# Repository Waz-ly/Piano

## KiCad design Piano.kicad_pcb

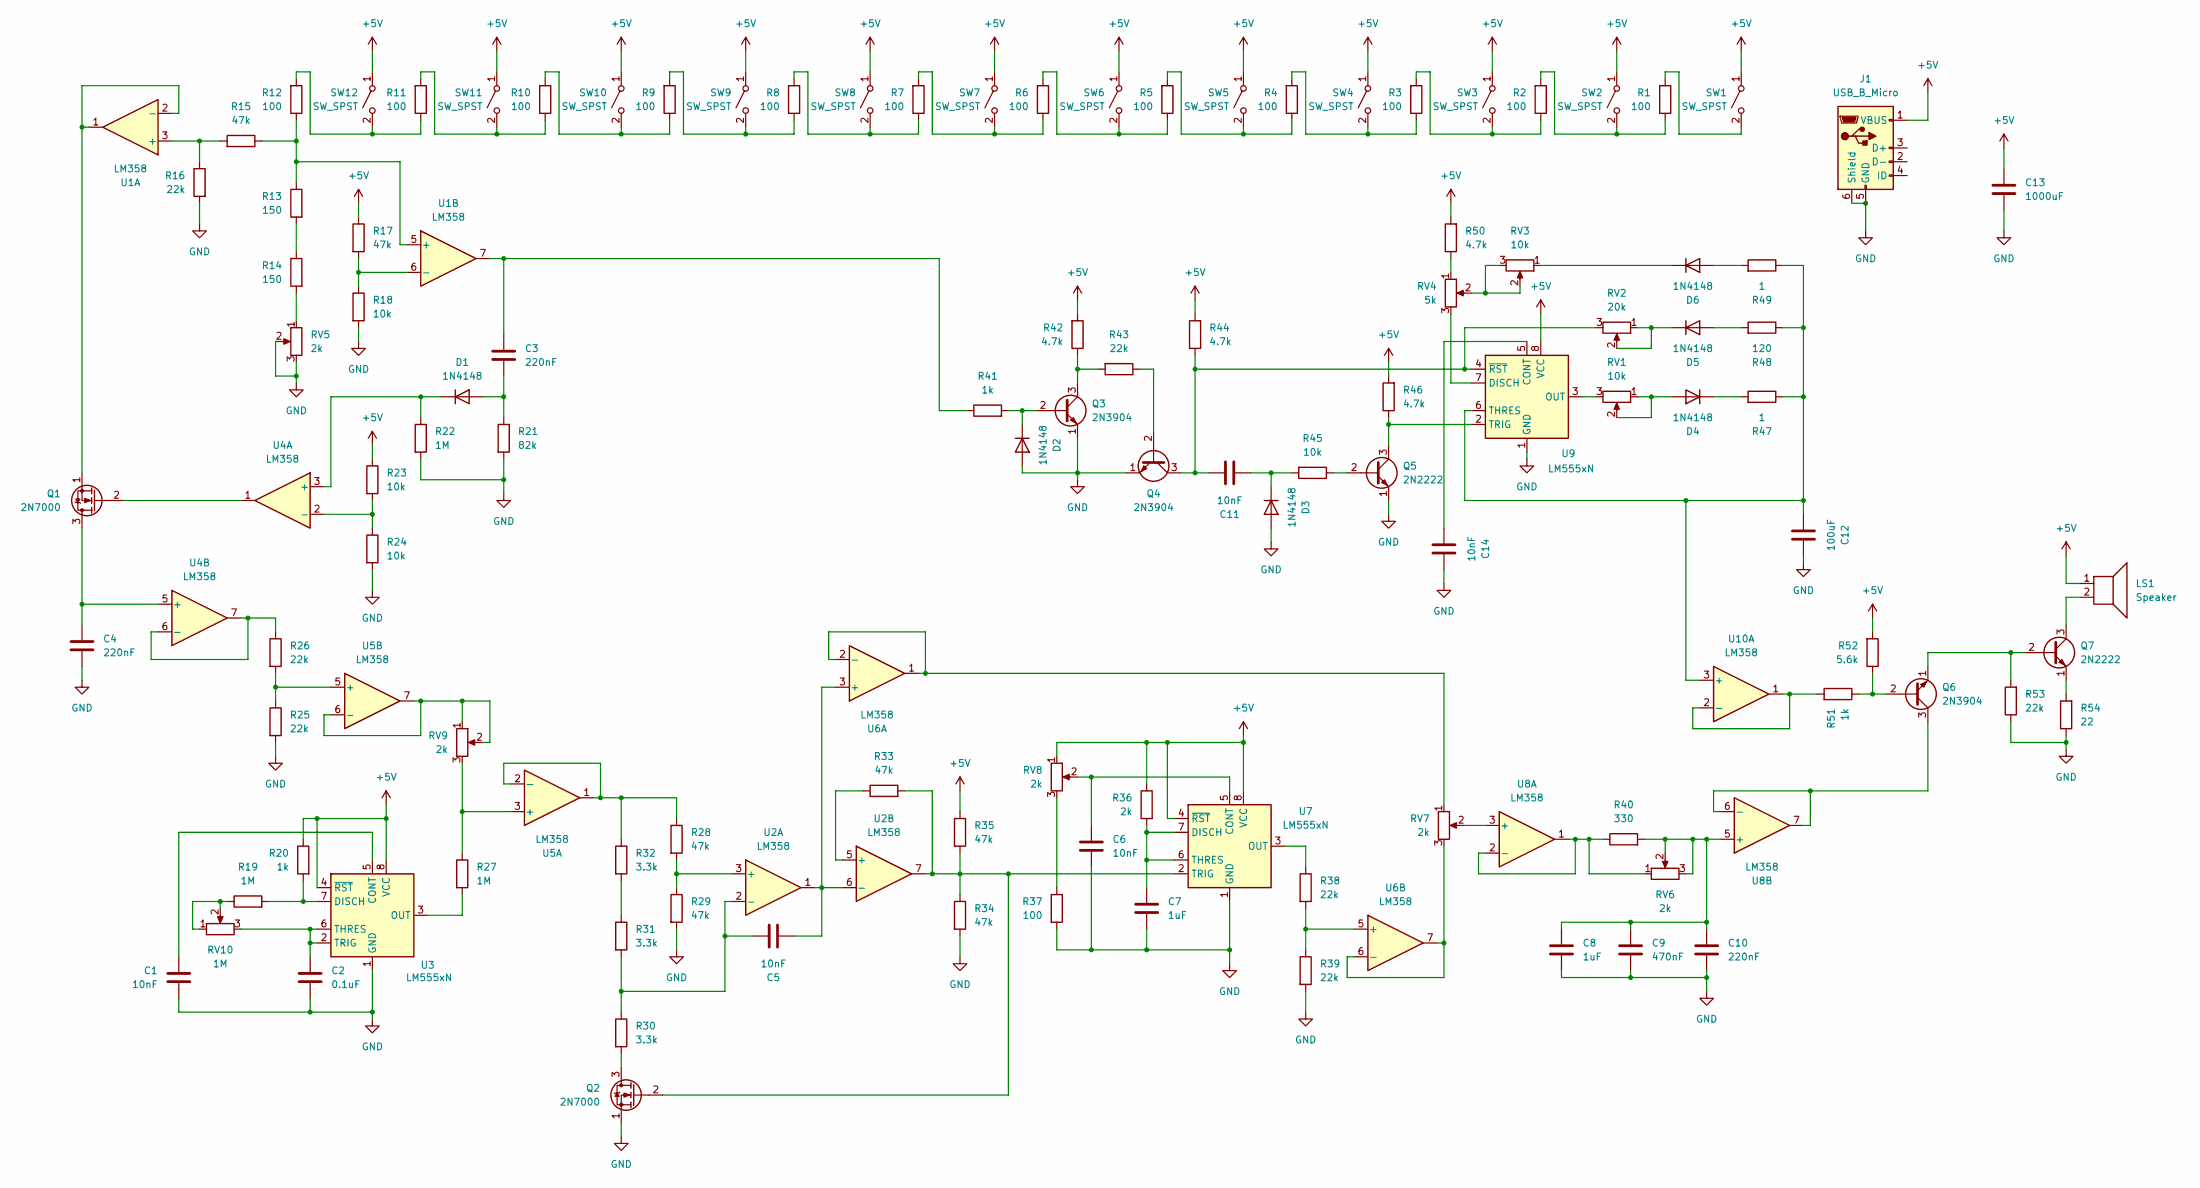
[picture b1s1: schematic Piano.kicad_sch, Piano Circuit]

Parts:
C1, C5, C6, C11, C14: 10nF; C_Rect_L7.2mm_W3.5mm_P5.00mm
C2: 0.1uF; C_Horizontal_D4.0mm_H7.0mm_P1.50mm
C3, C4, C10: 220nF; C_Rect_L7.2mm_W3.5mm_P5.00mm
C7, C8: 1uF; C_Axial_L5.1mm_D3.1mm_P10.00mm_Horizontal
C9: 470nF; C_Rect_L7.2mm_W3.5mm_P5.00mm
C12: 100uF; C_Horizontal_D5.0mm_H11.0mm_P2.00mm
C13: 1000uF; C_Horizontal_D10.0mm_H16.0mm_P5.00mm
D1, D2, D3, D4, D5, D6: 1N4148; D_DO-35_SOD27_P7.62mm_Horizontal
J1: USB_B_Micro; USB_Micro-B_XKB_U254-051T-4BH83-F1S
LS1: Speaker; PinHeader_1x02_P2.54mm_Vertical
Q1, Q2: 2N7000; TO-92_Inline
Q3, Q4, Q6: 2N3904; TO-92_Inline
Q5, Q7: 2N2222; TO-92_Inline
R1, R2, R3, R4, R5, R6, R7, R8, R9, R10, R11, R12, R37: 100; R_Axial_DIN0207_L6.3mm_D2.5mm_P10.16mm_Horizontal
R13, R14: 150; R_Axial_DIN0207_L6.3mm_D2.5mm_P10.16mm_Horizontal
R15, R17, R28, R29, R33, R34, R35: 47k; R_Axial_DIN0207_L6.3mm_D2.5mm_P10.16mm_Horizontal
R16, R25, R26, R38, R39, R43, R53: 22k; R_Axial_DIN0207_L6.3mm_D2.5mm_P10.16mm_Horizontal
R18, R23, R24, R45: 10k; R_Axial_DIN0207_L6.3mm_D2.5mm_P10.16mm_Horizontal
R19, R22, R27: 1M; R_Axial_DIN0207_L6.3mm_D2.5mm_P10.16mm_Horizontal
R20, R41, R51: 1k; R_Axial_DIN0207_L6.3mm_D2.5mm_P10.16mm_Horizontal
R21: 82k; R_Axial_DIN0207_L6.3mm_D2.5mm_P10.16mm_Horizontal
R30, R31, R32: 3.3k; R_Axial_DIN0207_L6.3mm_D2.5mm_P10.16mm_Horizontal
R36: 2k; R_Axial_DIN0207_L6.3mm_D2.5mm_P10.16mm_Horizontal
R40: 330; R_Axial_DIN0207_L6.3mm_D2.5mm_P10.16mm_Horizontal
R42, R44, R46, R50: 4.7k; R_Axial_DIN0207_L6.3mm_D2.5mm_P10.16mm_Horizontal
R47, R49: 1; R_Axial_DIN0207_L6.3mm_D2.5mm_P10.16mm_Horizontal
R48: 120; R_Axial_DIN0207_L6.3mm_D2.5mm_P10.16mm_Horizontal
R52: 5.6k; R_Axial_DIN0207_L6.3mm_D2.5mm_P10.16mm_Horizontal
R54: 22; R_Axial_DIN0207_L6.3mm_D2.5mm_P10.16mm_Horizontal
RV1, RV3: 10k; Inset_Potentiometer
RV2: 20k; Inset_Potentiometer
RV4: 5k; Inset_Potentiometer
RV5, RV6, RV7, RV8, RV9: 2k; Inset_Potentiometer
RV10: 1M; Inset_Potentiometer
SW1, SW2, SW3, SW4, SW5, SW6, SW7, SW8, SW9, SW10, SW11, SW12: SW_SPST; SW_Cherry_MX_Plate_1.00u
U1, U2, U4, U5, U6, U8, U10: LM358; DIP-8_W7.62mm
U3, U7, U9: LM555xN; DIP-8_W7.62mm

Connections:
+5V: C13.1, J1.1 (VBUS), LS1.1, R17.1, R20.1, R23.1, R35.1, R36.1, R42.2, R44.2, R46.2, R50.2, R52.2, RV8.1, SW1.1 (A), SW2.1 (A), SW3.1 (A), SW4.1 (A), SW5.1 (A), SW6.1 (A), SW7.1 (A), SW8.1 (A), SW9.1 (A), SW10.1 (A), SW11.1 (A), SW12.1 (A), U1.8 (V+), U2.8 (V+), U3.4 (~RST), U3.8 (VCC), U4.8 (V+), U5.8 (V+), U6.8 (V+), U7.4 (~RST), U7.8 (VCC), U8.8 (V+), U9.8 (VCC), U10.8 (V+)
GND: C1.2, C2.2, C4.2, C6.2, C7.2, C8.2, C9.2, C10.2, C12.1, C13.2, C14.1, D2.2 (A), D3.2 (A), J1.5 (GND), J1.6 (Shield), Q2.1 (S), Q3.1 (E), Q4.1 (E), Q5.1 (E), R16.2, R18.2, R21.2, R22.2, R24.2, R25.2, R29.2, R34.2, R37.2, R39.2, R53.1, R54.1, RV5.2, RV5.3, U1.4 (V-), U2.4 (V-), U3.1 (GND), U4.4 (V-), U5.4 (V-), U6.4 (V-), U7.1 (GND), U8.4 (V-), U9.1 (GND), U10.4 (V-)
unnamed: C3.1, R41.1, U1.7
unnamed: C3.2, D1.2 (A), R21.1
unnamed: D1.1 (K), R22.1, U4.3 (+)
unnamed: D2.1 (K), Q3.2 (B), R41.2
unnamed: C11.2, D3.1 (K), R45.2
unnamed: D4.2 (A), RV1.1, RV1.2
unnamed: D4.1 (K), R47.2
unnamed: D5.2 (A), R48.2
unnamed: D5.1 (K), RV2.1, RV2.2
unnamed: D6.2 (A), R49.2
unnamed: D6.1 (K), RV3.1
unnamed: C4.1, Q1.3 (D), U4.5 (+)
unnamed: Q1.2 (G), U4.1
unnamed: Q1.1 (S), U1.1, U1.2 (-)
unnamed: Q2.3 (D), R30.2
unnamed: Q2.2 (G), R33.2, R34.1, R35.2, U2.7, U7.2 (TRIG)
unnamed: Q3.3 (C), R42.1, R43.2
unnamed: Q4.2 (B), R43.1
unnamed: C11.1, Q4.3 (C), R44.1, RV2.3, U9.4 (~RST)
unnamed: Q5.2 (B), R45.1
unnamed: Q5.3 (C), R46.1, U9.2 (TRIG)
unnamed: Q6.2 (B), R51.1, R52.1
unnamed: Q6.3 (C), U8.6 (-), U8.7
unnamed: Q6.1 (E), Q7.2 (B), R53.2
unnamed: LS1.2, Q7.3 (C)
unnamed: Q7.1 (E), R54.2
unnamed: R13.2, R14.1
unnamed: R14.2, RV5.1
unnamed: R19.1, RV10.1, RV10.2
unnamed: R31.1, R32.2
unnamed: R37.1, RV8.3
unnamed: R50.1, RV4.1
unnamed: RV3.2, RV3.3, RV4.2
unnamed: R1.2, SW1.2 (B)
unnamed: R1.1, R2.2, SW2.2 (B)
unnamed: R2.1, R3.2, SW3.2 (B)
unnamed: R3.1, R4.2, SW4.2 (B)
unnamed: R4.1, R5.2, SW5.2 (B)
unnamed: R5.1, R6.2, SW6.2 (B)
unnamed: R6.1, R7.2, SW7.2 (B)
unnamed: R7.1, R8.2, SW8.2 (B)
unnamed: R8.1, R9.2, SW9.2 (B)
unnamed: R9.1, R10.2, SW10.2 (B)
unnamed: R10.1, R11.2, SW11.2 (B)
unnamed: R11.1, R12.2, SW12.2 (B)
unnamed: R15.2, R16.1, U1.3 (+)
unnamed: R12.1, R13.1, R15.1, U1.5 (+)
unnamed: R17.2, R18.1, U1.6 (-)
unnamed: R28.2, R29.1, U2.3 (+)
unnamed: C5.1, R30.1, R31.2, U2.2 (-)
unnamed: R33.1, U2.5 (+)
unnamed: C5.2, U2.1, U2.6 (-), U6.3 (+)
unnamed: C1.1, U3.5 (CONT)
unnamed: R19.2, R20.2, U3.7 (DISCH)
unnamed: R27.2, U3.3 (OUT)
unnamed: C2.1, RV10.3, U3.2 (TRIG), U3.6 (THRES)
unnamed: R23.2, R24.1, U4.2 (-)
unnamed: R26.1, U4.6 (-), U4.7
unnamed: R27.1, RV9.3, U5.3 (+)
unnamed: R28.1, R32.1, U5.1, U5.2 (-)
unnamed: R25.1, R26.2, U5.5 (+)
unnamed: RV9.1, RV9.2, U5.6 (-), U5.7
unnamed: RV7.1, U6.1, U6.2 (-)
unnamed: R38.2, R39.1, U6.5 (+)
unnamed: RV7.3, U6.6 (-), U6.7
unnamed: C6.1, RV8.2, U7.5 (CONT)
unnamed: C7.1, R36.2, U7.6 (THRES), U7.7 (DISCH)
unnamed: R38.1, U7.3 (OUT)
unnamed: RV7.2, U8.3 (+)
unnamed: R40.1, RV6.1, U8.1, U8.2 (-)
unnamed: C8.1, C9.1, C10.1, R40.2, RV6.2, RV6.3, U8.5 (+)
unnamed: C14.2, U9.5 (CONT)
unnamed: RV4.3, U9.7 (DISCH)
unnamed: RV1.3, U9.3 (OUT)
unnamed: C12.2, R47.1, R48.1, R49.1, U9.6 (THRES), U10.3 (+)
unnamed: R51.2, U10.1, U10.2 (-)

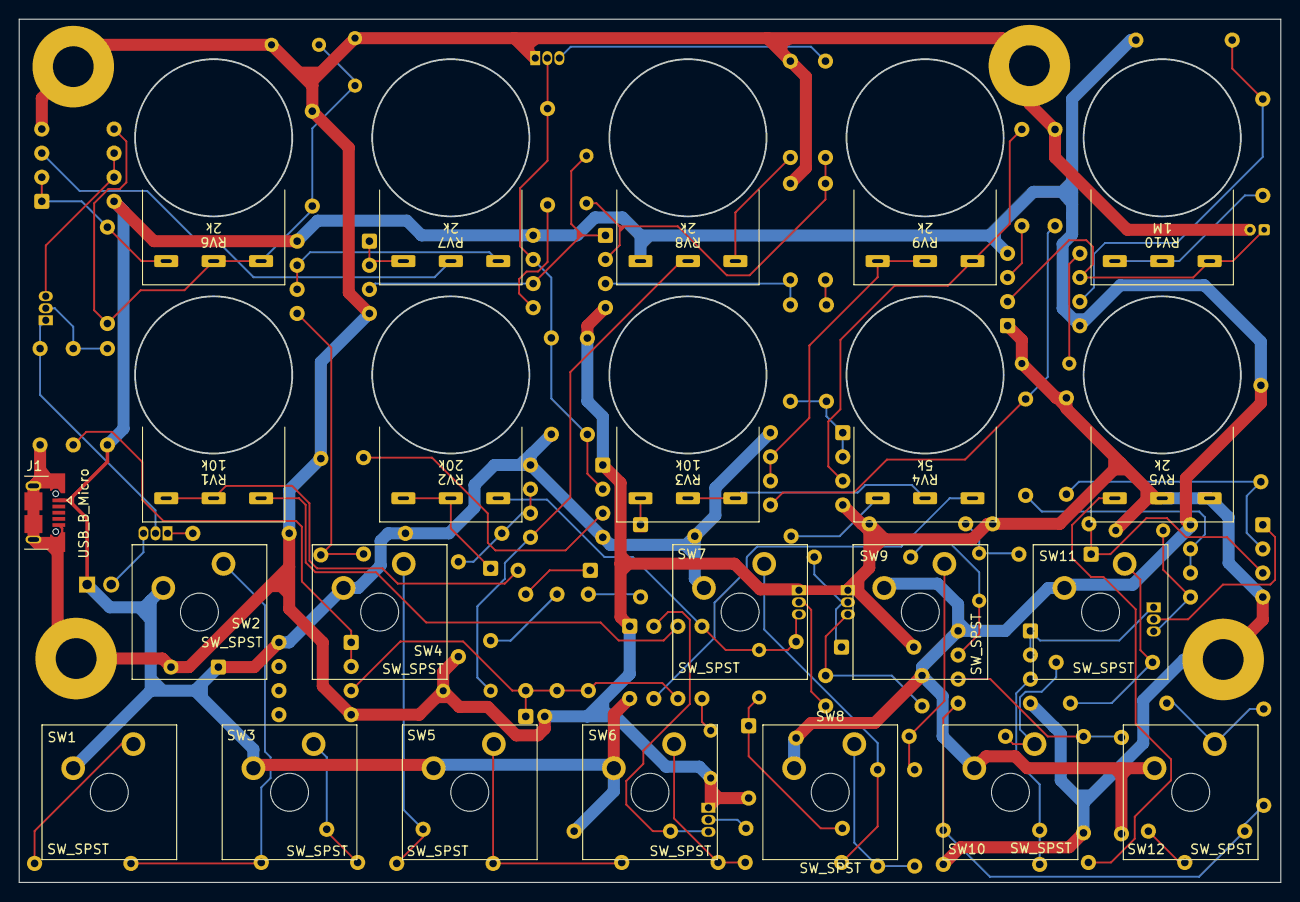
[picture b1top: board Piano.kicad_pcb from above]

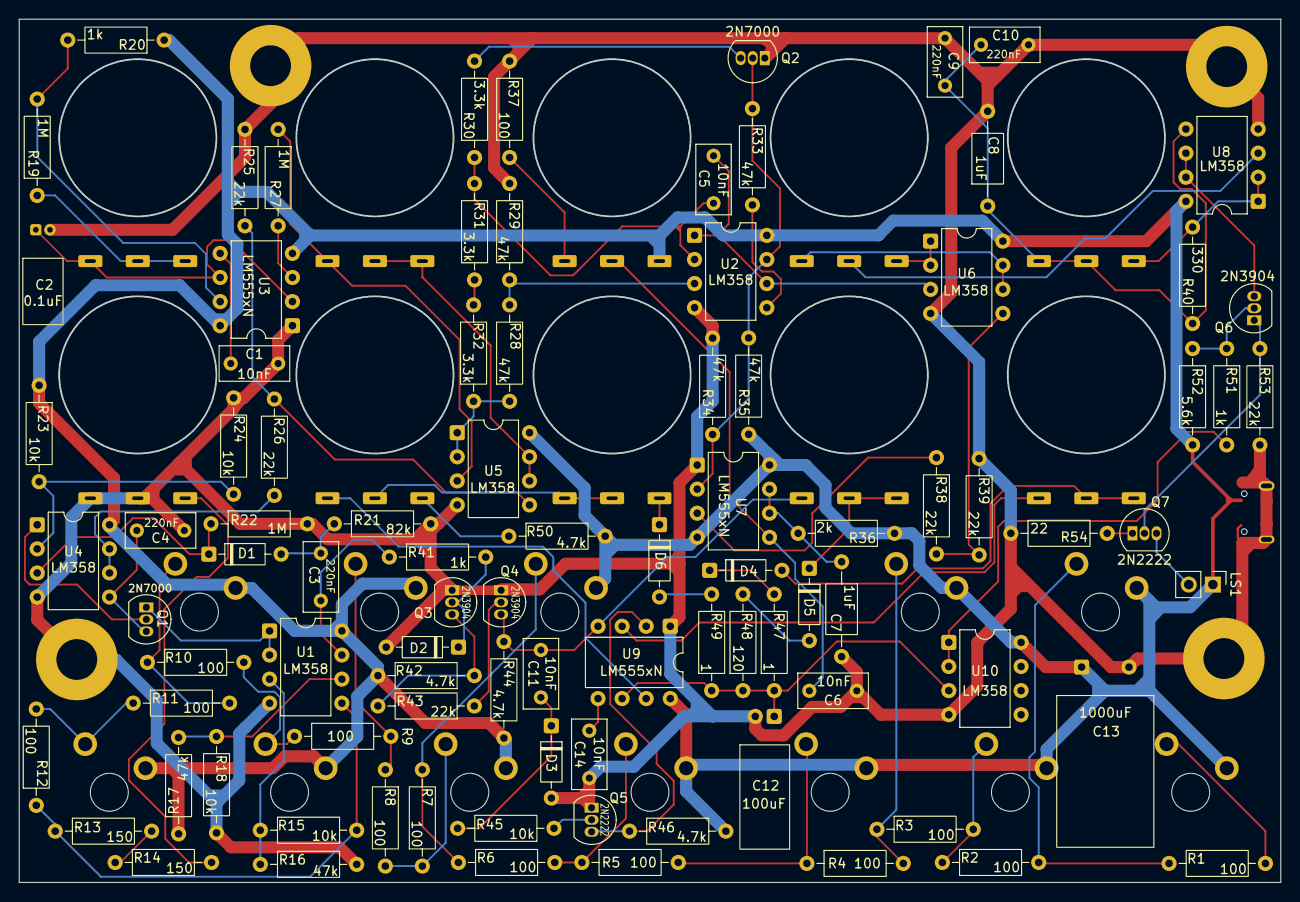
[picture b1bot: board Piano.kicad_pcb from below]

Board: 2 copper layers, 133.0 x 91.0 mm, 115 parts (92 on the bottom side), 78 nets.
